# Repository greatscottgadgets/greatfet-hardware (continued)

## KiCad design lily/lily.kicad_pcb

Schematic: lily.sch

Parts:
C1: 470nF; 0603; Part Number GRM188R61H474KA12D
C2, C3, C5: 100nF; 0603; Part Number GCM188L81H104KA57D
C4: 100pF; 0603; Part Number GQM1885C1H101JB01D
C6: 10nF; 0603; Part Number 885012206065
J1: NEIGHBOR1; HEADER-2x20; Part Number SSQ-120-23-G-D
J2: NEIGHBOR2; HEADER-2x20; Part Number SSQ-120-23-G-D
J3: ANT_IN; SMA-EDGE; Part Number CONREVSMA003.031
J4, J5, J6, J8, J9, J10, J12, J13, J14, J15, J16, J17, J18: TEST_2P; 0603-JUMPER
J7: BONUS_ROW; HEADER-1x20; Part Number SSQ-120-23-G-S
J11: Conn_01x02; Pin_Header_Straight_1x02_Pitch2.54mm
MH1, MH2, MH3, MH4: MOUNTING_HOLE; HOLE126MIL-COPPER
R1: 82.5; 0603; Part Number RMCF0603FT82R5
R2: 4.02; 0603; Part Number RMCF0603FT4R02
U1: ADL5904; QFN16-3; Part Number ADL5904ACPZN-R7

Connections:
/ADC0_0: J2.5, J10.2
/ADC0_2: J7.5
/ADC0_5: J7.4
/CLK0: J1.11
/CLK2: J2.12
/ENBL: J4.1, J5.1, J6.1, U1.14 (ENBL)
/I2C0_SCL: J2.40
/I2C0_SDA: J2.39
/P0_0: J1.4, J5.2
/P0_1: J1.6
/P1_0: J1.7
/P1_1: J1.10
/P1_2: J1.12
/P1_3: J1.40
/P1_4: J1.39
/P1_5: J1.13
/P1_6: J1.16
/P1_7: J1.15
/P1_8: J1.18
/P1_9: J1.17
/P1_10: J1.20, J13.1
/P1_11: J1.22, J12.1
/P1_12: J1.21
/P1_13: J1.26
/P1_14: J1.25
/P1_15: J1.28
/P1_16: J1.30
/P1_17: J1.32
/P1_18: J1.31
/P1_19: J1.38
/P1_20: J1.37
/P2_0: J1.35
/P2_1: J2.35
/P2_2: J2.33
/P2_3: J2.20
/P2_4: J2.19
/P2_5: J2.18, J17.2
/P2_6: J2.15
/P2_7: J2.14
/P2_8: J2.13
/P2_9: J7.6
/P2_10: J7.14
/P2_11: J7.13
/P2_12: J7.7
/P2_13: J7.8
/P3_0: J2.26
/P3_1: J2.24
/P3_2: J2.22
/P3_3: J2.32
/P3_4: J2.28
/P3_5: J2.37
/P3_6: J2.38
/P3_7: J2.30, J15.2
/P4_0: J2.4
/P4_2: J2.8
/P4_3: J2.9, J9.2
/P4_4: J2.7, U1.16 (VIN-)
/P4_5: J2.6
/P4_6: J2.10
/P4_7: J2.11
/P4_8: J2.3
/P4_9: J1.3, J4.2
/P4_10: J1.5, J6.2
/P5_0: J1.8
/P5_1: J1.9
/P5_2: J1.14
/P5_3: J1.19
/P5_4: J1.24
/P5_5: J1.23
/P5_6: J1.27
/P5_7: J1.29
/P6_0: J1.36
/P6_1: J7.18
/P6_2: J7.17
/P6_3: J2.36
/P6_4: J7.2
/P6_5: J7.3
/P6_6: J2.34
/P6_7: J2.31, J16.2
/P6_8: J2.29
/P6_9: J7.16
/P6_10: J7.15
/P7_0: J2.27
/P7_1: J2.25
/P7_2: J2.23
/P7_7: J2.16, J8.2
/P9_5: J1.33
/P9_6: J1.34
/PF_4: J2.21
/RESET: J7.11
/RF_IN: C1.1, U1.1 (RFIN)
/RTC_ALARM: J7.9
/VBAT: J7.12
/VBUS: J2.2
/VOUT: C6.1, J8.1, J9.1, J10.1, U1.10 (VRMS)
/WAKEUP0: J2.17, J18.2
/rms_avg: C5.2, R2.1, U1.4 (DECL)
GND: C2.2, C3.2, C4.2, C6.2, J1.1, J2.1, J3.2 (Ext), J7.1, J7.10, J7.19, J11.1, J14.1, MH1.1, MH2.1, MH3.1, MH4.1, R1.2, U1.0, U1.11 (GND)
unnamed: C1.2, J3.1 (In), R1.1
unnamed: C2.1, R2.2
unnamed: C5.1, U1.9 (CRMS)
unnamed: J11.2, U1.3 (VCAL)
unnamed: J12.2, J13.2, J14.2, U1.15 (RST)
unnamed: J15.1, J16.1, U1.13 (~Q~)
unnamed: J17.1, J18.1, U1.12 (Q)
VCC: C3.1, C4.1, J1.2, J7.20, U1.5 (VPOS), U1.7 (VPOS)

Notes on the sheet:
MISO
MOSI
SCK
SSEL
ISP
DFU
BOOT
jump to select output pin to ADC
jump to select on/off control pin
keep power decoupling capacitors near pin 5
470nF ac coupling capacitor should give frequency coverage down to tens of kHz
Crms = 100nF change for more/less averaging
RST grounded by default
jump to select Q and ~Q~

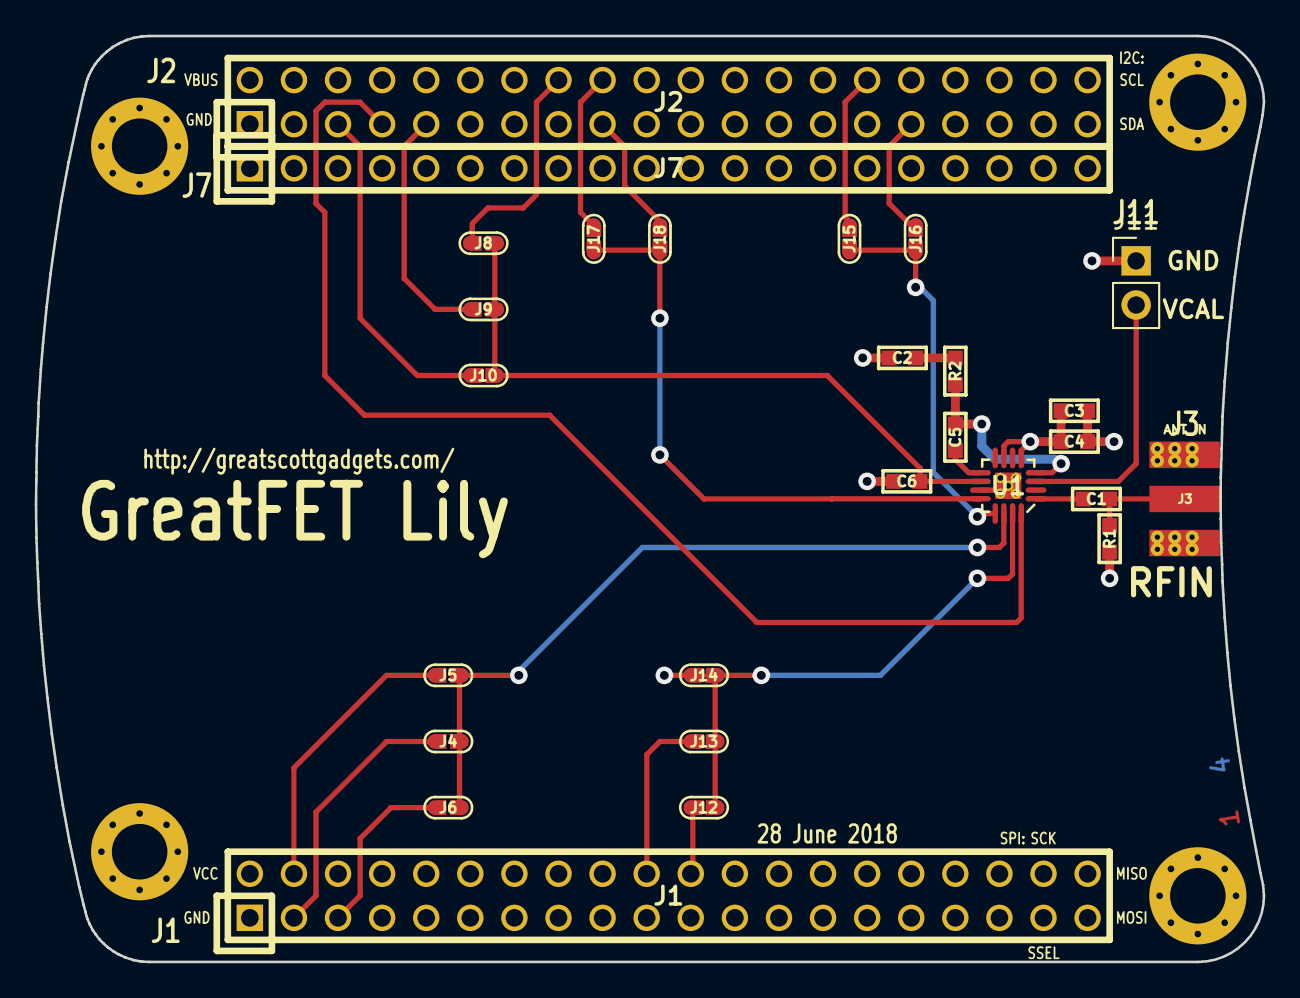
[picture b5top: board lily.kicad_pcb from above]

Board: 4 copper layers, 70.7 x 53.3 mm, 31 parts (0 on the bottom side), 26 nets.

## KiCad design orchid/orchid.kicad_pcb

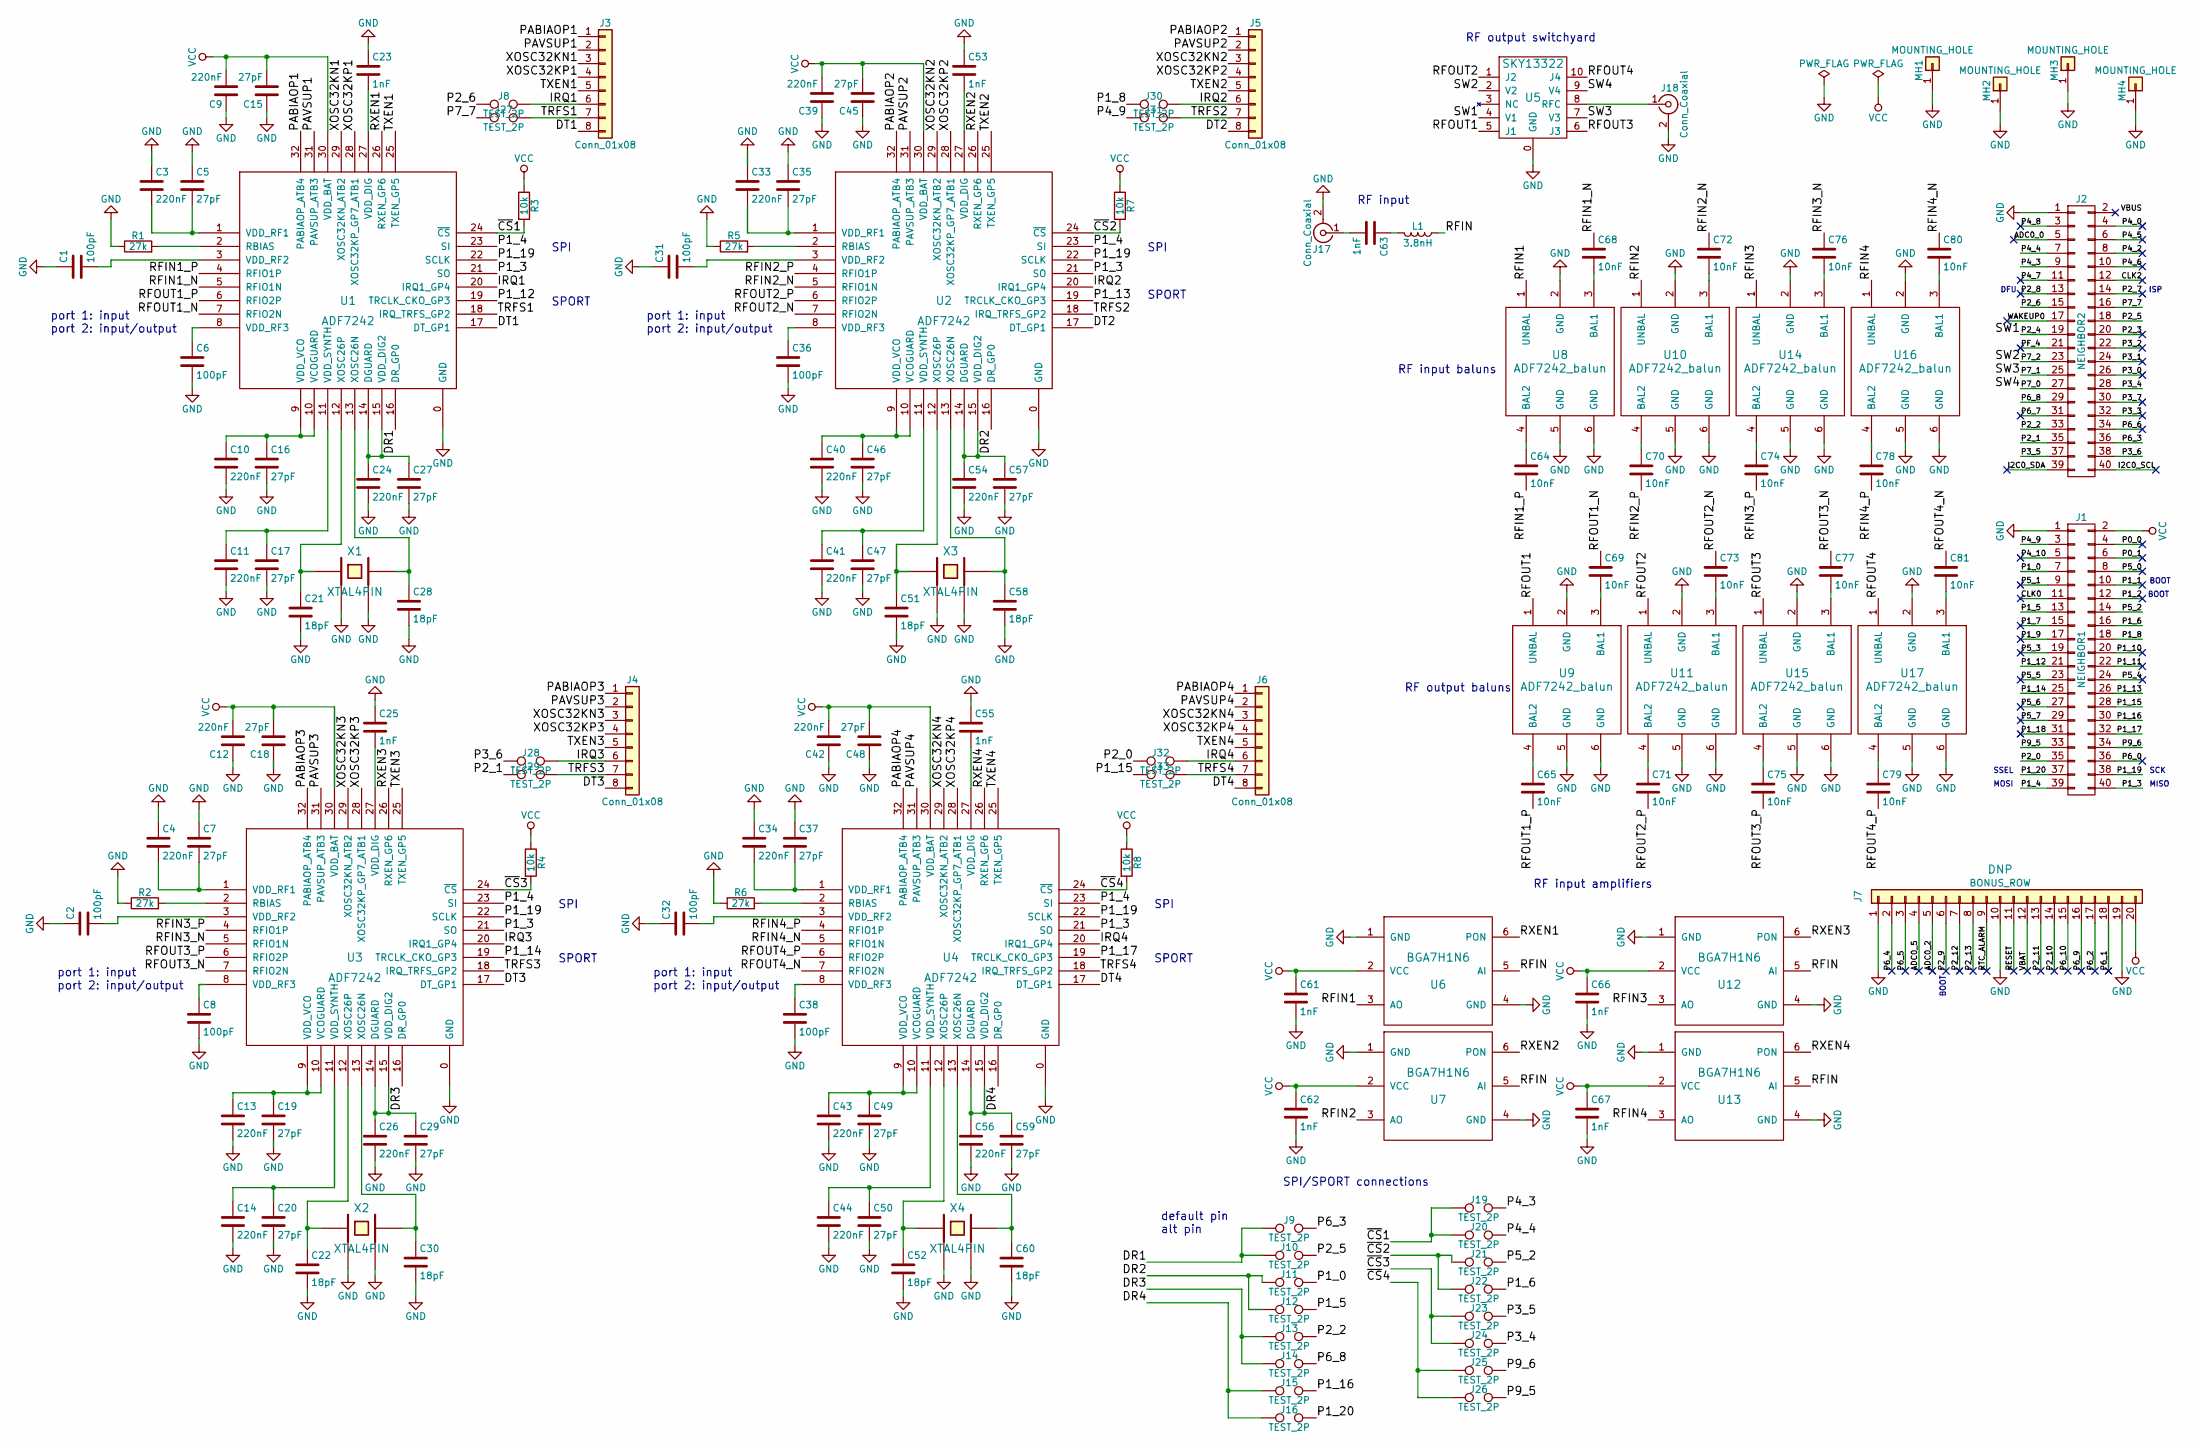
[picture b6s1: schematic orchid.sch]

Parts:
C1, C2, C6, C8, C31, C32, C36, C38: 100pF; 0402; Part Number 732-7533-1-ND
C3, C4, C9, C10, C11, C12, C13, C14, C24, C26, C33, C34, C39, C40, C41, C42, C43, C44, C54, C56: 220nF; 0402; Part Number 732-7488-1-ND
C5, C7, C15, C16, C17, C18, C19, C20, C27, C29, C35, C37, C45, C46, C47, C48, C49, C50, C57, C59: 27pF; 0402; Part Number 399-8960-1-ND
C21, C22, C28, C30, C51, C52, C58, C60: 18pF; 0402; Part Number 399-8952-1-ND
C23, C25, C53, C55, C61, C62, C63, C66, C67: 1nF; 0402; Part Number 732-7501-1-ND
C64, C65, C68, C69, C70, C71, C72, C73, C74, C75, C76, C77, C78, C79, C80, C81: 10nF; 0402; Part Number 732-7507-1-ND
J1: NEIGHBOR1; HEADER-2x20; Part Number SSQ-120-23-G-D
J2: NEIGHBOR2; HEADER-2x20; Part Number SSQ-120-23-G-D
J3, J4, J5, J6: Conn_01x08; HEADER-2x4; Part Number S5750-04-ND
J7: BONUS_ROW; HEADER-1x20; Part Number SSQ-120-23-G-S
J8, J9, J10, J11, J12, J13, J14, J15, J16, J19, J20, J21, J22, J23, J24, J25, J26, J27, J28, J29, J30, J31, J32, J33: TEST_2P; 0603-JUMPER
J17, J18: Conn_Coaxial; SMA-EDGE; Part Number CONREVSMA003.062-ND
L1: 3.8nH; 0402; Part Number 535-10379-1-ND
MH1, MH2, MH3, MH4: MOUNTING_HOLE; HOLE126MIL-COPPER
R1, R2, R5, R6: 27k; 0402; Part Number RMCF0402JT27K0CT-ND
R3, R4, R7, R8: 10k; 0402; Part Number RMCF0402JT10K0CT-ND
U1, U2, U3, U4: ADF7242; LFCSP32; Part Number ADF7242BCPZ-ND
U5: SKY13322; SKY13322-375LF; Part Number 863-1176-1-ND
U6, U7, U12, U13: BGA7H1N6; TSNP-6-2; Part Number BGA7H1N6E6327XTSA1CT-ND
U8, U9, U10, U11, U14, U15, U16, U17: ADF7242_balun; Part Number 712-1575-1-ND
X1, X2, X3, X4: XTAL4PIN; XTAL3.2x2.5mm; Part Number 644-1101-1-ND

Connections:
/ADC0_0: J2.5
/ADC0_2: J7.5
/ADC0_5: J7.4
/CLK0: J1.11
/CLK2: J2.12
/DR1: J9.1, J10.1, U1.16 (DR_GP0)
/DR2: J11.1, J12.1, U2.16 (DR_GP0)
/DR3: J13.1, J14.1, U3.16 (DR_GP0)
/DR4: J15.1, J16.1, U4.16 (DR_GP0)
/DT1: J3.8, U1.17 (DT_GP1)
/DT2: J5.8, U2.17 (DT_GP1)
/DT3: J4.8, U3.17 (DT_GP1)
/DT4: J6.8, U4.17 (DT_GP1)
/I2C0_SCL: J2.40
/I2C0_SDA: J2.39
/IRQ1: J3.6, J8.2, U1.20 (IRQ1_GP4)
/IRQ2: J5.6, J30.2, U2.20 (IRQ1_GP4)
/IRQ3: J4.6, J28.2, U3.20 (IRQ1_GP4)
/IRQ4: J6.6, J32.2, U4.20 (IRQ1_GP4)
/P0_0: J1.4
/P0_1: J1.6
/P1_0: J1.7, J11.2
/P1_1: J1.10
/P1_2: J1.12
/P1_3: J1.40, U1.21 (SO), U2.21 (SO), U3.21 (SO), U4.21 (SO)
/P1_4: J1.39, U1.23 (SI), U2.23 (SI), U3.23 (SI), U4.23 (SI)
/P1_5: J1.13, J12.2
/P1_6: J1.16, J22.2
/P1_7: J1.15
/P1_8: J1.18, J30.1
/P1_9: J1.17
/P1_10: J1.20
/P1_11: J1.22
/P1_12: J1.21, U1.19 (TRCLK_CKO_GP3)
/P1_13: J1.26, U2.19 (TRCLK_CKO_GP3)
/P1_14: J1.25, U3.19 (TRCLK_CKO_GP3)
/P1_15: J1.28, J33.1
/P1_16: J1.30, J15.2
/P1_17: J1.32, U4.19 (TRCLK_CKO_GP3)
/P1_18: J1.31
/P1_19: J1.38, U1.22 (SCLK), U2.22 (SCLK), U3.22 (SCLK), U4.22 (SCLK)
/P1_20: J1.37, J16.2
/P2_0: J1.35, J32.1
/P2_1: J2.35, J29.1
/P2_2: J2.33, J13.2
/P2_3: J2.20
/P2_4: J2.19, U5.4 (V1)
/P2_5: J2.18, J10.2
/P2_6: J2.15, J8.1
/P2_7: J2.14
/P2_8: J2.13
/P2_9: J7.6
/P2_10: J7.14
/P2_11: J7.13
/P2_12: J7.7
/P2_13: J7.8
/P3_0: J2.26
/P3_1: J2.24
/P3_2: J2.22
/P3_3: J2.32
/P3_4: J2.28, J24.2
/P3_5: J2.37, J23.2
/P3_6: J2.38, J28.1
/P3_7: J2.30
/P4_0: J2.4
/P4_2: J2.8
/P4_3: J2.9, J19.2
/P4_4: J2.7, J20.2
/P4_5: J2.6
/P4_6: J2.10
/P4_7: J2.11
/P4_8: J2.3
/P4_9: J1.3, J31.1
/P4_10: J1.5
/P5_0: J1.8
/P5_1: J1.9
/P5_2: J1.14, J21.2
/P5_3: J1.19
/P5_4: J1.24
/P5_5: J1.23
/P5_6: J1.27
/P5_7: J1.29
/P6_0: J1.36
/P6_1: J7.18
/P6_2: J7.17
/P6_3: J2.36, J9.2
/P6_4: J7.2
/P6_5: J7.3
/P6_6: J2.34
/P6_7: J2.31
/P6_8: J2.29, J14.2
/P6_9: J7.16
/P6_10: J7.15
/P7_0: J2.27, U5.9 (V4)
/P7_1: J2.25, U5.7 (V3)
/P7_2: J2.23, U5.2 (V2)
/P7_7: J2.16, J27.1
/P9_5: J1.33, J26.2
/P9_6: J1.34, J25.2
/PABIAOP1: J3.1, U1.32 (PABIAOP_ATB4)
/PABIAOP2: J5.1, U2.32 (PABIAOP_ATB4)
/PABIAOP3: J4.1, U3.32 (PABIAOP_ATB4)
/PABIAOP4: J6.1, U4.32 (PABIAOP_ATB4)
/PAVSUP1: J3.2, U1.31 (PAVSUP_ATB3)
/PAVSUP2: J5.2, U2.31 (PAVSUP_ATB3)
/PAVSUP3: J4.2, U3.31 (PAVSUP_ATB3)
/PAVSUP4: J6.2, U4.31 (PAVSUP_ATB3)
/PF_4: J2.21
/RESET: J7.11
/RFIN: L1.1, U6.5 (AI), U7.5 (AI), U12.5 (AI), U13.5 (AI)
/RFIN1: U6.3 (AO), U8.1 (UNBAL)
/RFIN1_N: C68.1, U1.5 (RFIO1N)
/RFIN1_P: C64.2, U1.4 (RFIO1P)
/RFIN2: U7.3 (AO), U10.1 (UNBAL)
/RFIN2_N: C72.1, U2.5 (RFIO1N)
/RFIN2_P: C70.2, U2.4 (RFIO1P)
/RFIN3: U12.3 (AO), U14.1 (UNBAL)
/RFIN3_N: C76.1, U3.5 (RFIO1N)
/RFIN3_P: C74.2, U3.4 (RFIO1P)
/RFIN4: U13.3 (AO), U16.1 (UNBAL)
/RFIN4_N: C80.1, U4.5 (RFIO1N)
/RFIN4_P: C78.2, U4.4 (RFIO1P)
/RFOUT1: U5.5 (J1), U9.1 (UNBAL)
/RFOUT1_N: C69.1, U1.7 (RFIO2N)
/RFOUT1_P: C65.2, U1.6 (RFIO2P)
/RFOUT2: U5.1 (J2), U11.1 (UNBAL)
/RFOUT2_N: C73.1, U2.7 (RFIO2N)
/RFOUT2_P: C71.2, U2.6 (RFIO2P)
/RFOUT3: U5.6 (J3), U15.1 (UNBAL)
/RFOUT3_N: C77.1, U3.7 (RFIO2N)
/RFOUT3_P: C75.2, U3.6 (RFIO2P)
/RFOUT4: U5.10 (J4), U17.1 (UNBAL)
/RFOUT4_N: C81.1, U4.7 (RFIO2N)
/RFOUT4_P: C79.2, U4.6 (RFIO2P)
/RTC_ALARM: J7.9
/RXEN1: U1.26 (RXEN_GP6), U6.6 (PON)
/RXEN2: U2.26 (RXEN_GP6), U7.6 (PON)
/RXEN3: U3.26 (RXEN_GP6), U12.6 (PON)
/RXEN4: U4.26 (RXEN_GP6), U13.6 (PON)
/TRFS1: J3.7, J27.2, U1.18 (IRQ_TRFS_GP2)
/TRFS2: J5.7, J31.2, U2.18 (IRQ_TRFS_GP2)
/TRFS3: J4.7, J29.2, U3.18 (IRQ_TRFS_GP2)
/TRFS4: J6.7, J33.2, U4.18 (IRQ_TRFS_GP2)
/TXEN1: J3.5, U1.25 (TXEN_GP5)
/TXEN2: J5.5, U2.25 (TXEN_GP5)
/TXEN3: J4.5, U3.25 (TXEN_GP5)
/TXEN4: J6.5, U4.25 (TXEN_GP5)
/VBAT: J7.12
/WAKEUP0: J2.17
/XOSC32KN1: J3.3, U1.29 (XOSC32KN_ATB2)
/XOSC32KN2: J5.3, U2.29 (XOSC32KN_ATB2)
/XOSC32KN3: J4.3, U3.29 (XOSC32KN_ATB2)
/XOSC32KN4: J6.3, U4.29 (XOSC32KN_ATB2)
/XOSC32KP1: J3.4, U1.28 (XOSC32KP_GP7_ATB1)
/XOSC32KP2: J5.4, U2.28 (XOSC32KP_GP7_ATB1)
/XOSC32KP3: J4.4, U3.28 (XOSC32KP_GP7_ATB1)
/XOSC32KP4: J6.4, U4.28 (XOSC32KP_GP7_ATB1)
/~CS~1: J19.1, J20.1, R3.2, U1.24 (~CS~)
/~CS~2: J21.1, J22.1, R7.2, U2.24 (~CS~)
/~CS~3: J23.1, J24.1, R4.2, U3.24 (~CS~)
/~CS~4: J25.1, J26.1, R8.2, U4.24 (~CS~)
GND: C1.1, C2.1, C3.1, C4.1, C5.1, C6.2, C7.1, C8.2, C9.1, C10.2, C11.2, C12.1, C13.2, C14.2, C15.1, C16.2, C17.2, C18.1, C19.2, C20.2, C21.2, C22.2, C23.1, C24.2, C25.1, C26.2, C27.2, C28.2, C29.2, C30.2, C31.1, C32.1, C33.1, C34.1, C35.1, C36.2, C37.1, C38.2, C39.1, C40.2, C41.2, C42.1, C43.2, C44.2, C45.1, C46.2, C47.2, C48.1, C49.2, C50.2, C51.2, C52.2, C53.1, C54.2, C55.1, C56.2, C57.2, C58.2, C59.2, C60.2, C61.2, C62.2, C66.2, C67.2, J1.1, J2.1, J7.1, J7.10, J7.19, J17.2 (Ext), J18.2 (Ext), MH1.1, MH2.1, MH3.1, MH4.1, R1.1, R2.1, R5.1, R6.1, U1.0 (GND), U2.0 (GND), U3.0 (GND), U4.0 (GND), U5.0 (GND), U6.1 (GND), U6.4 (GND), U7.1 (GND), U7.4 (GND), U8.2 (GND), U8.5 (GND), U8.6 (GND), U9.2 (GND), U9.5 (GND), U9.6 (GND), U10.2 (GND), U10.5 (GND), U10.6 (GND), U11.2 (GND), U11.5 (GND), U11.6 (GND), U12.1 (GND), U12.4 (GND), U13.1 (GND), U13.4 (GND), U14.2 (GND), U14.5 (GND), U14.6 (GND), U15.2 (GND), U15.5 (GND), U15.6 (GND), U16.2 (GND), U16.5 (GND), U16.6 (GND), U17.2 (GND), U17.5 (GND), U17.6 (GND), X1.2, X1.4, X2.2, X2.4, X3.2, X3.4, X4.2, X4.4
unnamed: C1.2, U1.3 (VDD_RF2)
unnamed: C2.2, U3.3 (VDD_RF2)
unnamed: C3.2, C5.2, U1.1 (VDD_RF1)
unnamed: C4.2, C7.2, U3.1 (VDD_RF1)
unnamed: C6.1, U1.8 (VDD_RF3)
unnamed: C8.1, U3.8 (VDD_RF3)
unnamed: C10.1, C16.1, U1.9 (VDD_VCO), U1.10 (VCOGUARD)
unnamed: C11.1, C17.1, U1.11 (VDD_SYNTH)
unnamed: C13.1, C19.1, U3.9 (VDD_VCO), U3.10 (VCOGUARD)
unnamed: C14.1, C20.1, U3.11 (VDD_SYNTH)
unnamed: C21.1, U1.12 (XOSC26P), X1.1
unnamed: C22.1, U3.12 (XOSC26P), X2.1
unnamed: C23.2, U1.27 (VDD_DIG)
unnamed: C24.1, C27.1, U1.14 (DGUARD), U1.15 (VDD_DIG2)
unnamed: C25.2, U3.27 (VDD_DIG)
unnamed: C26.1, C29.1, U3.14 (DGUARD), U3.15 (VDD_DIG2)
unnamed: C28.1, U1.13 (XOSC26N), X1.3
unnamed: C30.1, U3.13 (XOSC26N), X2.3
unnamed: C31.2, U2.3 (VDD_RF2)
unnamed: C32.2, U4.3 (VDD_RF2)
unnamed: C33.2, C35.2, U2.1 (VDD_RF1)
unnamed: C34.2, C37.2, U4.1 (VDD_RF1)
unnamed: C36.1, U2.8 (VDD_RF3)
unnamed: C38.1, U4.8 (VDD_RF3)
unnamed: C40.1, C46.1, U2.9 (VDD_VCO), U2.10 (VCOGUARD)
unnamed: C41.1, C47.1, U2.11 (VDD_SYNTH)
unnamed: C43.1, C49.1, U4.9 (VDD_VCO), U4.10 (VCOGUARD)
unnamed: C44.1, C50.1, U4.11 (VDD_SYNTH)
unnamed: C51.1, U2.12 (XOSC26P), X3.1
unnamed: C52.1, U4.12 (XOSC26P), X4.1
unnamed: C53.2, U2.27 (VDD_DIG)
unnamed: C54.1, C57.1, U2.14 (DGUARD), U2.15 (VDD_DIG2)
unnamed: C55.2, U4.27 (VDD_DIG)
unnamed: C56.1, C59.1, U4.14 (DGUARD), U4.15 (VDD_DIG2)
unnamed: C58.1, U2.13 (XOSC26N), X3.3
unnamed: C60.1, U4.13 (XOSC26N), X4.3
unnamed: C63.1, L1.2
unnamed: C63.2, J17.1 (In)
unnamed: C64.1, U8.4 (BAL2)
unnamed: C65.1, U9.4 (BAL2)
unnamed: C68.2, U8.3 (BAL1)
unnamed: C69.2, U9.3 (BAL1)
unnamed: C70.1, U10.4 (BAL2)
unnamed: C71.1, U11.4 (BAL2)
unnamed: C72.2, U10.3 (BAL1)
unnamed: C73.2, U11.3 (BAL1)
unnamed: C74.1, U14.4 (BAL2)
unnamed: C75.1, U15.4 (BAL2)
unnamed: C76.2, U14.3 (BAL1)
unnamed: C77.2, U15.3 (BAL1)
unnamed: C78.1, U16.4 (BAL2)
unnamed: C79.1, U17.4 (BAL2)
unnamed: C80.2, U16.3 (BAL1)
unnamed: C81.2, U17.3 (BAL1)
unnamed: J18.1 (In), U5.8 (RFC)
unnamed: R1.2, U1.2 (RBIAS)
unnamed: R2.2, U3.2 (RBIAS)
unnamed: R5.2, U2.2 (RBIAS)
unnamed: R6.2, U4.2 (RBIAS)
VCC: C9.2, C12.2, C15.2, C18.2, C39.2, C42.2, C45.2, C48.2, C61.1, C62.1, C66.1, C67.1, J1.2, J7.20, R3.1, R4.1, R7.1, R8.1, U1.30 (VDD_BAT), U2.30 (VDD_BAT), U3.30 (VDD_BAT), U4.30 (VDD_BAT), U6.2 (VCC), U7.2 (VCC), U12.2 (VCC), U13.2 (VCC)

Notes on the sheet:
MISO
MOSI
SCK
SSEL
ISP
DFU
BOOT
port 1: input port 2: input/output
RF output switchyard
RF output baluns
SPI
SPORT
SPI/SPORT connections
default pin alt pin
RF input baluns
RF input amplifiers
RF input

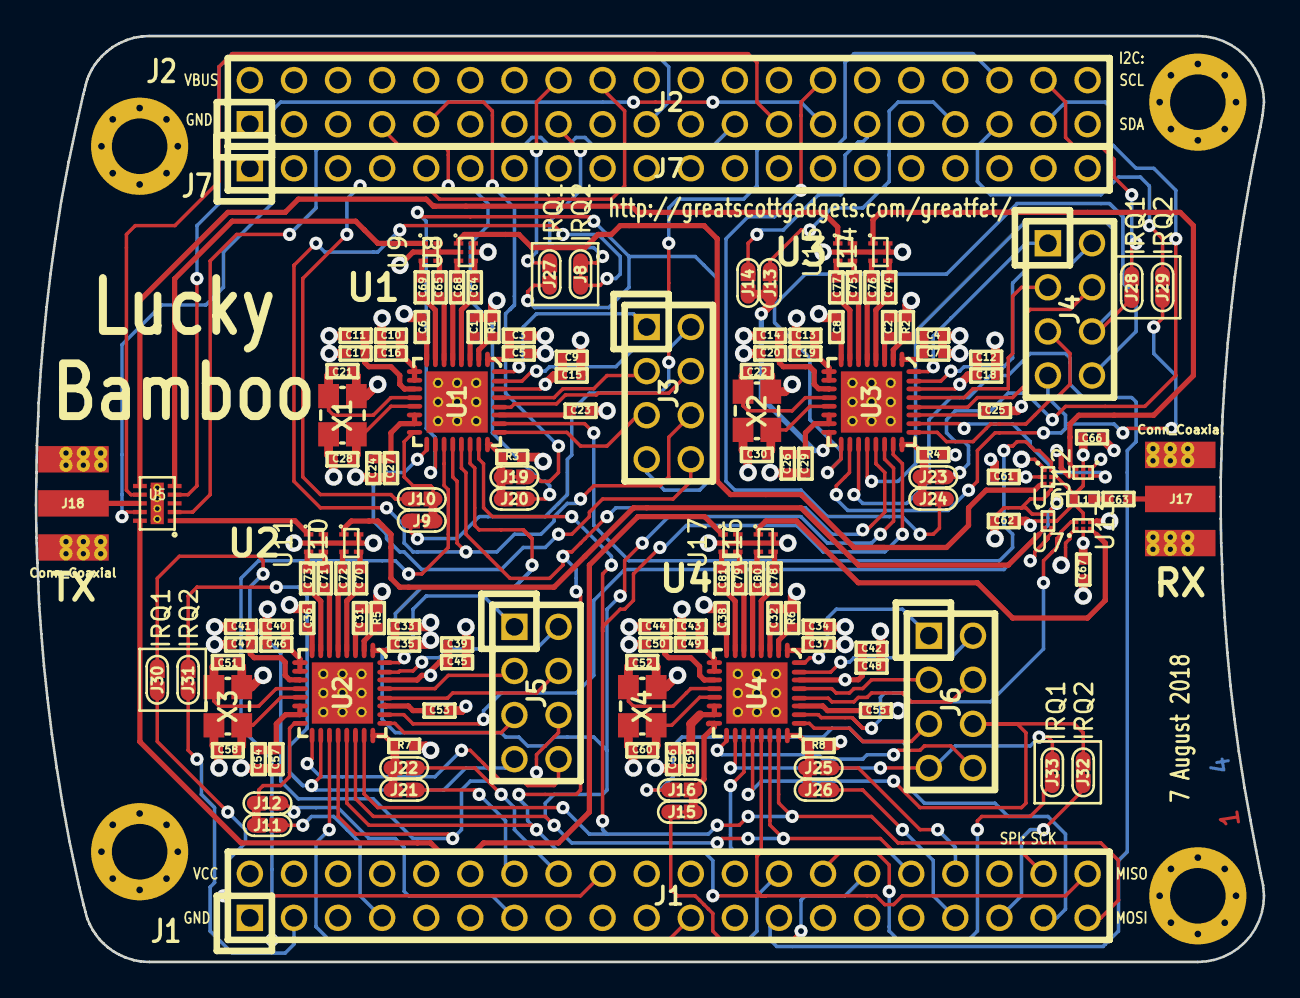
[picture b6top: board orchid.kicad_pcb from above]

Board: 4 copper layers, 70.7 x 53.3 mm, 148 parts (0 on the bottom side), 165 nets.
